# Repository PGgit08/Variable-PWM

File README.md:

# Variable-PWM
A printed circuit board that generates a PWM signal.

## Description
### How It Works (and Specs)
Variable-PWM is a PCB that generates a PWM signal. It was designed with [Autodesk Eagle](https://www.autodesk.com/products/eagle/overview?term=1-YEAR&tab=subscription) and manufactured by [JLCPCB](https://jlcpcb.com/). It produces a pulse width modulation (PWM) square-wave signal. This signal can be modified with potentiometers **VR1** and **VR2**. **VR1** changes the signal's *frequency*, which can either range from around **0.7 HZ - 7 HZ (SLOW MODE)** or **19.7 HZ - 216.7 HZ (FAST MODE)**. Switch **S1** sets the board to **FAST MODE** if it is switched to the *left*, and it sets the board to **SLOW MODE** if it is switched to the *right*. Potentiometer **VR2** controls the signal's *duty cycle* which ranges from **0% - ~100%**. LED **D1** indicates the signal produced by the board by flashing on and off depending on the signal. **[Click here for an in-depth explanation.](/Docs/Explanation.md)**

### Board Images (Front and Back)

## How To Use the Board
**The board should be powered with a 9V Battery.** Use the **+** and **-** pins to power the board. Use the **OUT** pin for the output signal, and the **GND** pin for connecting to the *board's* ground. Information on how to use the switch and potentiometers can be found **[here](https://github.com/PGgit08/Variable-PWM#how-it-works)**. Click **[here](/Simulation/SimVideos.md)** to see this board in action. 

## Design and Parts
### Design Hardware
The schematic and board files can be found in **[the Hardware folder](/Hardware)**. Gerber files for production are in **[this](/Production/Variable_PWM.zip)** zip folder. Also, an image of the schematic can also be seen right **[here](/Hardware/Variable_PWM.pdf)**.

### Parts Required
- LM358P Dual Operational Amplifier DIP-8 **(x1)** -> [Amazon Link](https://www.amazon.com/gp/product/B07WQWPLSP/)
- NE555 Timer DIP-8 **(x1)** -> [Amazon Link](https://www.amazon.com/gp/product/B07WR9B4JT)
- 10 uF Electrolytic Capacitor @50V (Generic) **(x4)**
- 100 uF Electrolytic Capacitor @50V (Generic) **(x1)**
- 0.1 uF Ceramic Capacitor @>9V (Generic) **(x1)**
- 10K Potentiometer **(x2)** -> [SparkFun Link](https://www.sparkfun.com/products/9806)
- DIP-8 IC Socket **(x2)** -> [SparkFun Link](https://www.sparkfun.com/products/7937)
- 10K Resistor (Generic) **(x4)** 
- 1K Resistor (Generic) **(x4)** 
- 3 Pin Slideswitch **(x1)** -> [Amazon Link](https://www.amazon.com/gp/product/B09R42XQTB)
- Male Header Pin (Generic) **(x4)**
- NPN Transistor @200mA/40V (Generic) **(x1)**
- LED @3V (Generic) **(x1)**

### **SCHEMATIC BASED ON SPARKFUN LIBRARIES -> [HERE](https://github.com/sparkfun/SparkFun-Eagle-Libraries)**

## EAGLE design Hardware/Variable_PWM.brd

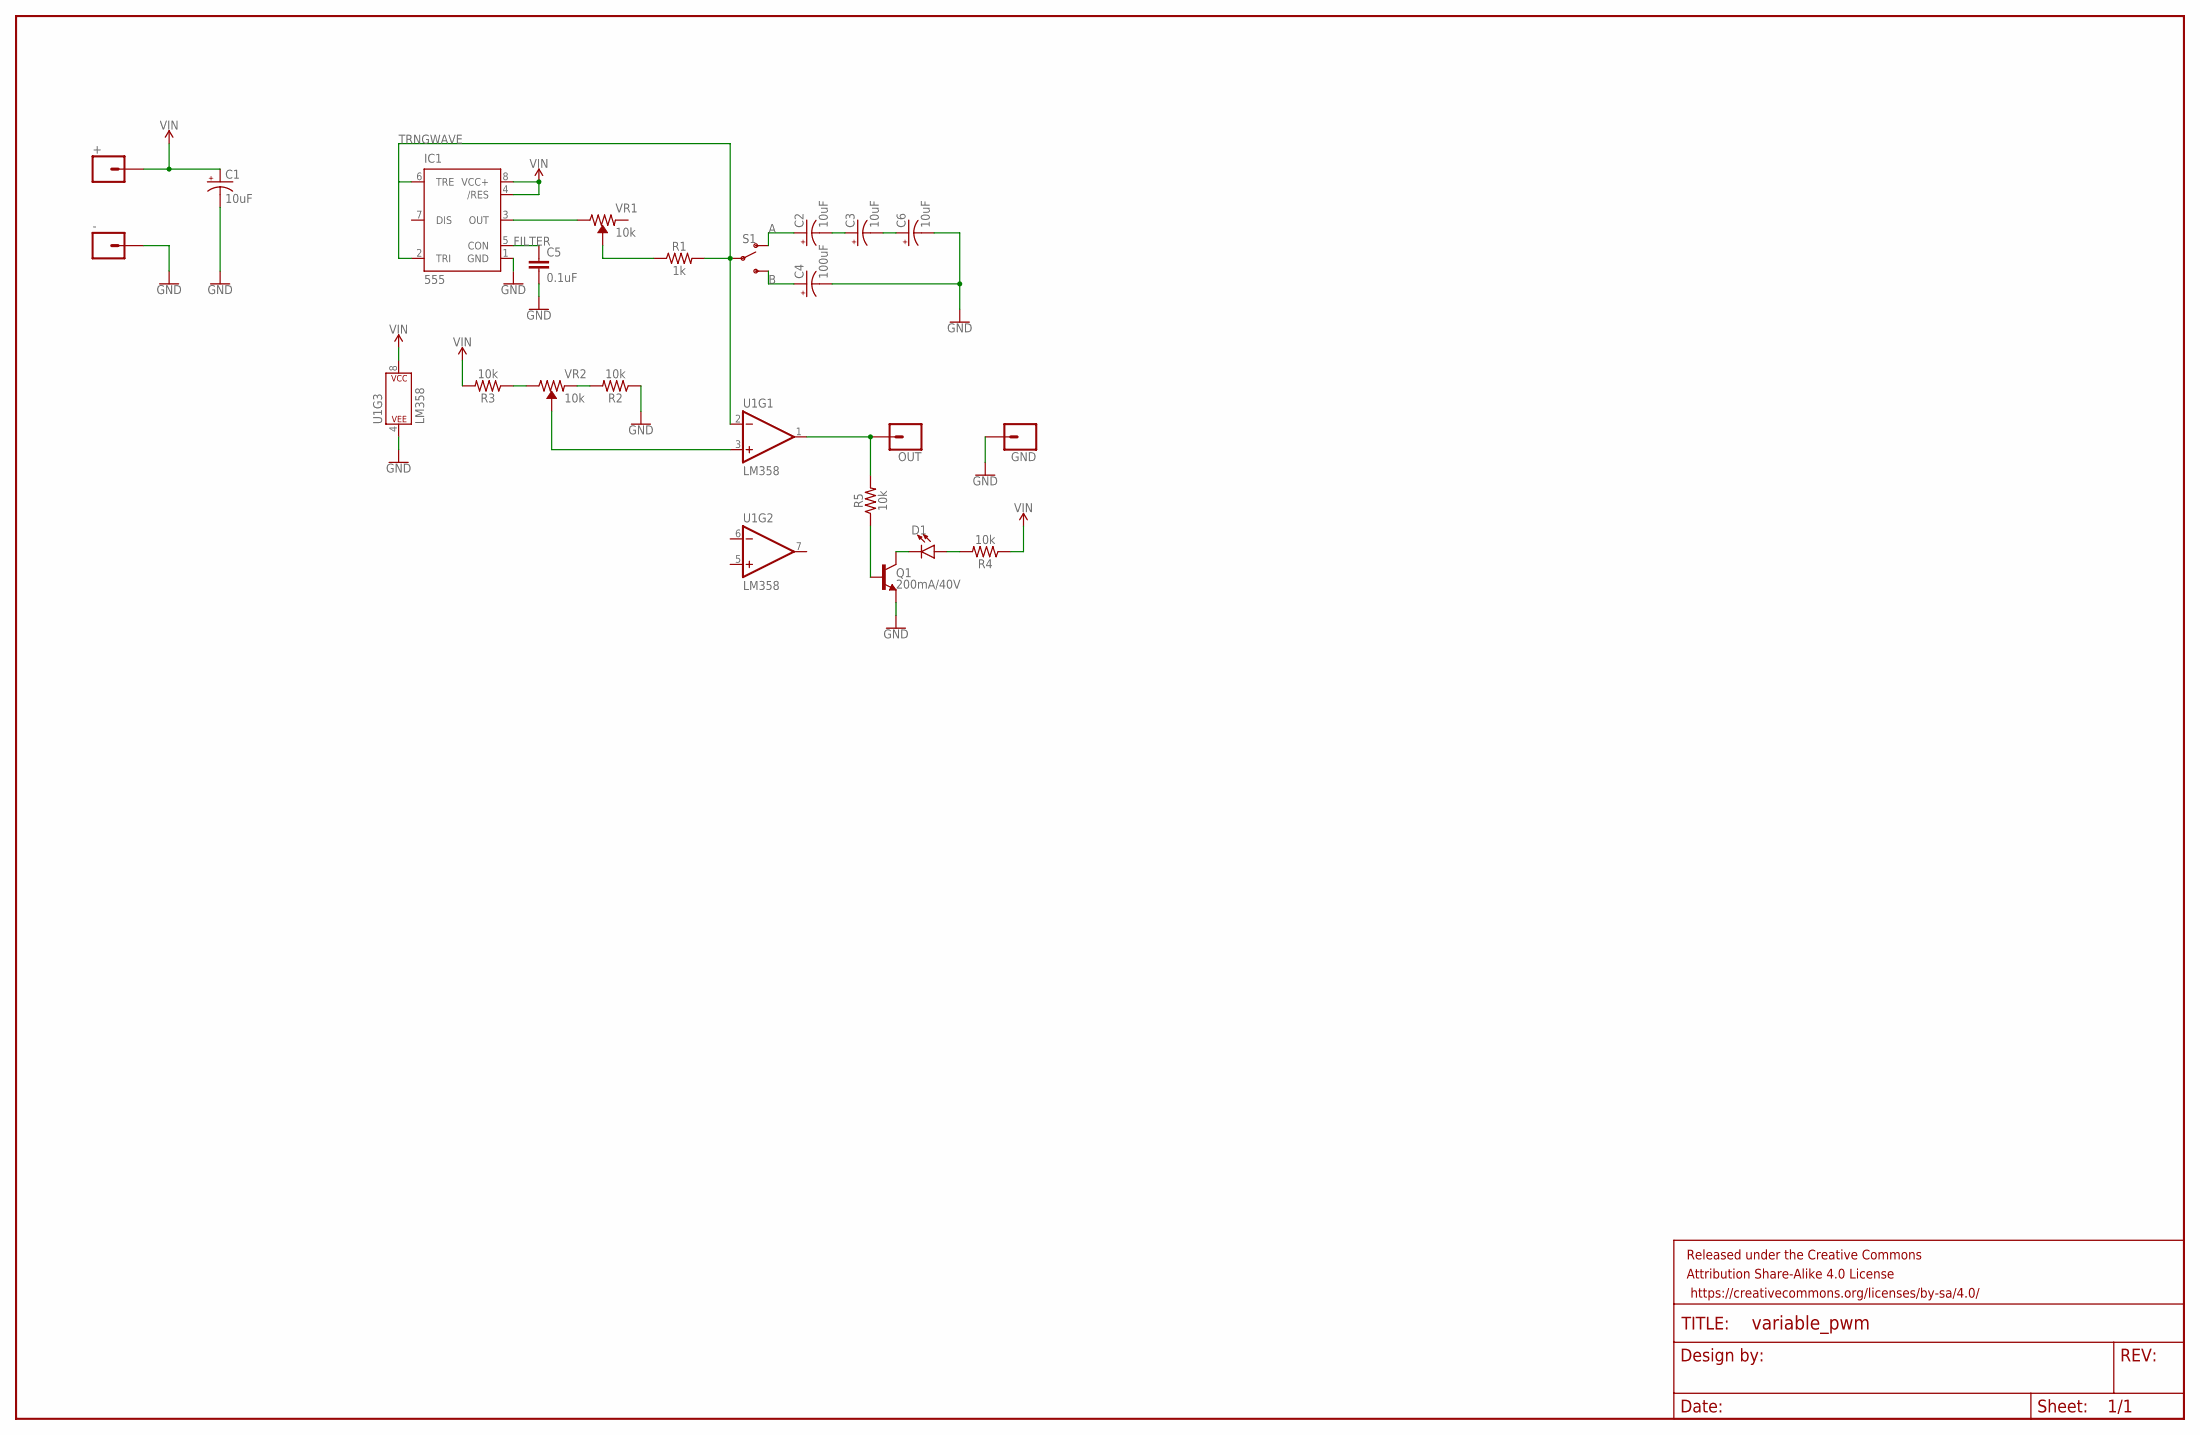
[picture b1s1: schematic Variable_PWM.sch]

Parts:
+: CONN_01; 1X01
-: CONN_01; 1X01
C1, C2, C3, C6: 10uF; CPOL-RADIAL-2.5MM-5MM
C4: 100uF; CPOL-RADIAL-2.5MM-6.5MM
C5: 0.1uF; CAP-PTH-SMALL-KIT
D1: LED5MM; LED_5MM
FRAME1: FRAME-LEDGERNO_FOOTPRINT; DUMMY
GND: CONN_01; 1X01
IC1: 555; DIP08
OUT: CONN_01; 1X01
Q1: 200mA/40V; TO-92
R1: 1k; AXIAL-0.3
R2, R3, R4, R5: 10k; AXIAL-0.3
S1: SWITCH-SPDT-PTH-11.6X4.0MM; SWITCH_SPDT_PTH_11.6X4.0MM
U1: LM358; DIP08
VR1, VR2: 10k; TRIMPOT-PTH-3386U

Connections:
A: C2.1 (+), S1.1 (O)
B: C4.1 (+), S1.3 (S)
FILTER: C5.1, IC1.5 (CON)
GND: -.1, C1.2 (-), C4.2 (-), C5.2, C6.2 (-), GND.1, IC1.1 (GND), Q1.1 (E), R2.P$1 (1), U1.4 (P$V-)
unnamed: C2.2 (-), C3.1 (+)
unnamed: C3.2 (-), C6.1 (+)
unnamed: R1.P$1 (1), VR1.2 (WIPER)
unnamed: IC1.3 (OUT), VR1.3 (CW)
unnamed: R2.P$2 (2), VR2.1 (CCW)
unnamed: R3.P$1 (1), VR2.3 (CW)
unnamed: U1.3 (+IN), VR2.2 (WIPER)
unnamed: D1.A, R4.P$2 (2)
unnamed: D1.K (C), Q1.3 (C)
unnamed: Q1.2 (B), R5.P$1 (1)
OUT: OUT.1, R5.P$2 (2), U1.1 (OUT)
TRNGWAVE: IC1.2 (TRI), IC1.6 (TRE), R1.P$2 (2), S1.2, U1.2 (-IN)
VIN: +.1, C1.1 (+), IC1.4 (/RES), IC1.8 (VCC+), R3.P$2 (2), R4.P$1 (1), U1.8 (P$V+)

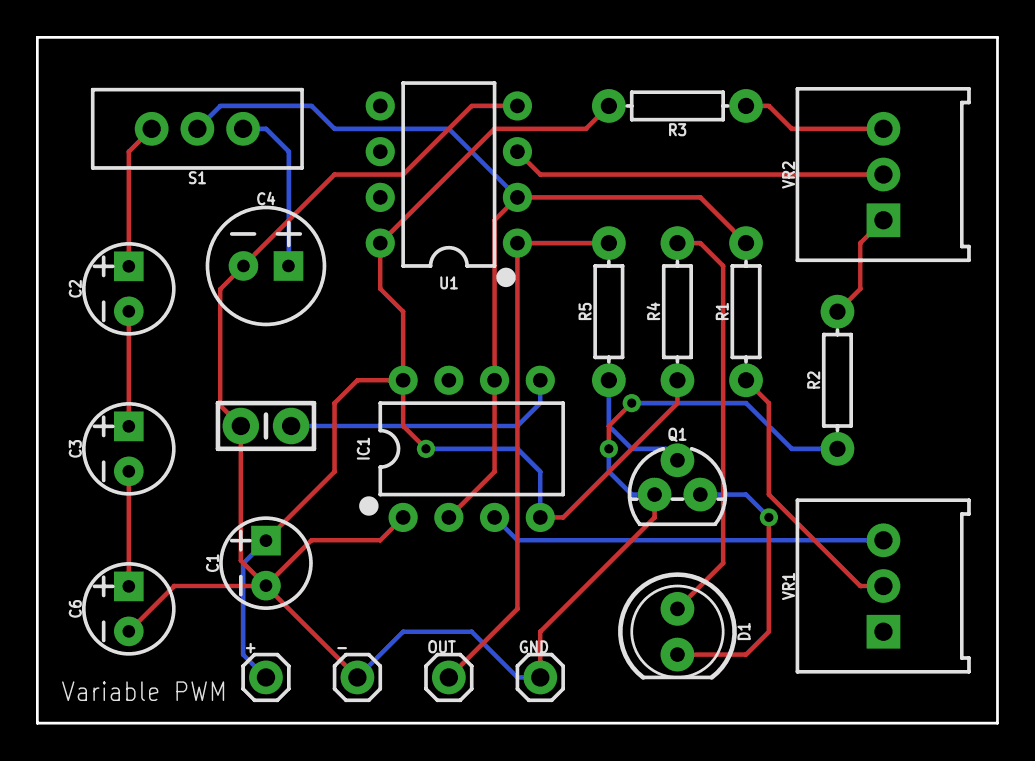
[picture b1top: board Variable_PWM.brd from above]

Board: 2 copper layers, 53.3 x 38.1 mm, 23 parts (0 on the bottom side), 17 nets.

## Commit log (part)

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2022-11-05 created project folders
2022-11-06 added hardware and production files
2022-11-06 added SVG image of schematic
2022-11-06 updated readme.md and added new doc
2022-11-06 added in depth explanation
2022-11-06 added pdf image of schematic
2022-11-06 added video simulation
2022-11-06 updates readme and sim videos
2022-11-13 image files for explanation changed
2022-11-13 pcb images changed

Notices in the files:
parts and their libraries:
SparkFun-Connectors: Licensing: Creative Commons ShareAlike 4.0 International - https://creativecommons.org/licenses/by-sa/4.0
SparkFun-Aesthetics: Released under the Creative Commons Attribution Share-Alike 4.0 License
SparkFun-Aesthetics: https://creativecommons.org/licenses/by-sa/4.0
